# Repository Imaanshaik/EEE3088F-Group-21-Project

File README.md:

# EEE3088F-Group-21-Project

Micro-mouse Sensing and Power Modules
Welcome to the GitHub repository for the Sensing and Power Modules of the Micro-mouse project. This repository contains the design files, documentation, and code related to the development of the sensor and power subsystems for the Micro-mouse robot.

Repository Contents:
Sensing Module:

Schematics
PCB design files
Bill of Materials (BOM)
Code for sensor data processing
Power Module:

Power circuit schematics
PCB layout files
Power management code
Documentation:

Interim Design Report
Final Report
README file
Getting Started:
To get started with the project, follow these steps:

Clone the repository to your local machine:

git clone (https://github.com/Imaanshaik/EEE3088F-Group-21-Project)
Navigate to the respective folders for the Sensing and Power Modules to access the design files and documentation.

Review the README files within each module for specific instructions on setup and usage.

Contributing:
If you would like to contribute to the development of the Sensing and Power Modules, please follow these guidelines:

Fork the repository to your GitHub account.
Create a new branch for your feature or bug fix:
git checkout -b feature/new-feature
Make your changes and commit them with descriptive messages:
git commit -m "Add new sensor calibration code"
Push your changes to your fork:
git push origin feature/new-feature
Open a pull request to merge your changes into the main repository.
Contact:
For any questions or feedback regarding the Sensing and Power Modules, please contact us at [mxxsaf002@myuct.ac.za (sensing module) and shkima005@myuct.ac.za (power module)].

We look forward to collaborating with you on this exciting project!

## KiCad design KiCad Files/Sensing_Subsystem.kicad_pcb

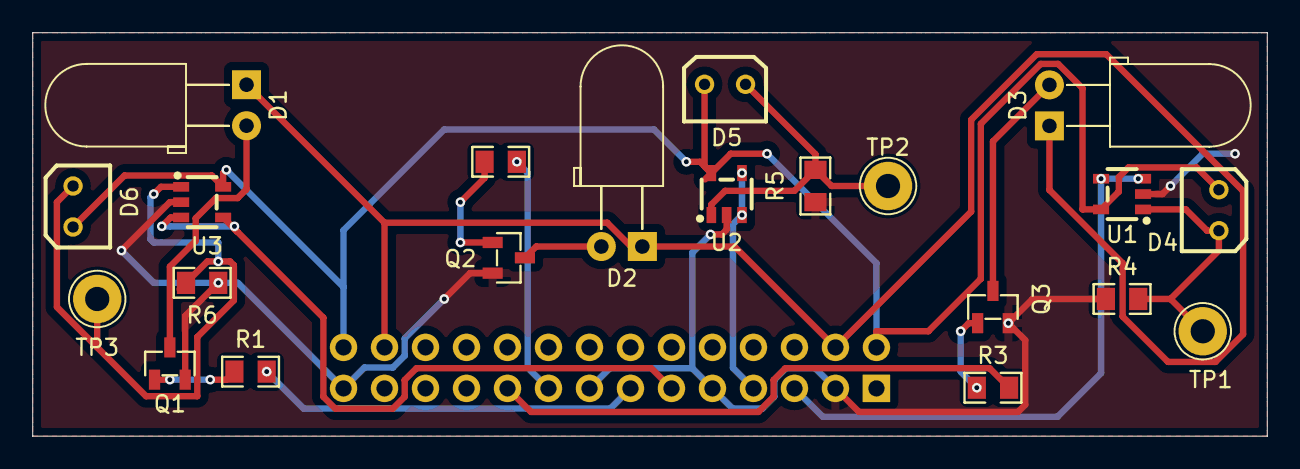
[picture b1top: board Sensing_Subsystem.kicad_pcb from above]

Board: 2 copper layers, 76.5 x 25.0 mm, 22 parts (1 on the bottom side), 18 nets.

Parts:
D1, D2, D3: SFH 4544; LED_D5.0mm_Horizontal_O3.81mm_Z15.0mm
D4, D5, D6: BPW41N; SENSOR-TH_BPW41N
J1: Conn_02x14_Odd_Even; PinHeader_2x14_P2.54mm_Vertical
Q1, Q2, Q3: MMBT2222A_C8512; babytransistor
R1, R2, R3: 6.8k; 6.8kresistor
R4, R5, R6: 1M; 6.8kresistor
TP1, TP2, TP3: TestPoint; TestPoint_THTPad_D3.0mm_Drill1.5mm
U1, U2, U3: LMV321IDBVR; opamp

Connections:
+3.3V: D4.2 (C), D5.2 (C), D6.2 (C), J1.2, J1.28, U1.5 (V+), U2.5 (V+), U3.5 (V+)
BATT: D1.1 (A), D2.1 (A), D3.1 (A), J1.4, J1.26
GND: J1.3, J1.9, J1.15, J1.27, Q1.2 (E), Q2.2 (E), Q3.2 (E), R4.1, R5.1, R6.1, U1.2 (GND), U2.2 (GND), U3.2 (GND)
unnamed: D1.2 (C), Q1.3 (C)
unnamed: D2.2 (C), Q2.3 (C)
unnamed: D3.2 (C), Q3.3 (C)
unnamed: D4.1 (A), R4.2, TP1.1, U1.1 (+)
unnamed: D5.1 (A), R5.2, TP2.1, U2.1 (+)
unnamed: D6.1 (A), R6.2, TP3.1, U3.1 (+)
unnamed: Q1.1 (B), R1.2
unnamed: Q2.1 (B), R2.2
unnamed: Q3.1 (B), R3.2
PA3: J1.5, U1.3 (-), U1.4 (OUT)
PA4: J1.7, U2.3 (-), U2.4 (OUT)
PA5: J1.11, U3.3 (-), U3.4 (OUT)
PA6: J1.13, R1.1
PA7: J1.17, R2.1
PC4: J1.19, R3.1

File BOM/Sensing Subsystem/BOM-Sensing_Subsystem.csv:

Comment,Designator,Footprint,LCSC
BPW41N,"D4,D5,D6",SENSOR-TH_BPW41N,C142586
1M,"R4,R5,R6",6.8kresistor,C17514
6.8k,"R1,R2,R3",6.8kresistor,C17772
SFH 4544,"D1,D2,D3",LED_D5.0mm_Horizontal_O3.81mm_Z15.0mm,C2900370
LMV321IDBVR,"U1,U2,U3",opamp,C7972
MMBT2222A_C8512,"Q1,Q2,Q3",babytransistor,C8512
TestPoint,TP2,TestPoint_THTPad_D3.0mm_Drill1.5mm,
TestPoint,TP3,TestPoint_THTPad_D3.0mm_Drill1.5mm,
TestPoint,TP1,TestPoint_THTPad_D3.0mm_Drill1.5mm,
Conn_02x14_Odd_Even,J1,PinHeader_2x14_P2.54mm_Vertical,

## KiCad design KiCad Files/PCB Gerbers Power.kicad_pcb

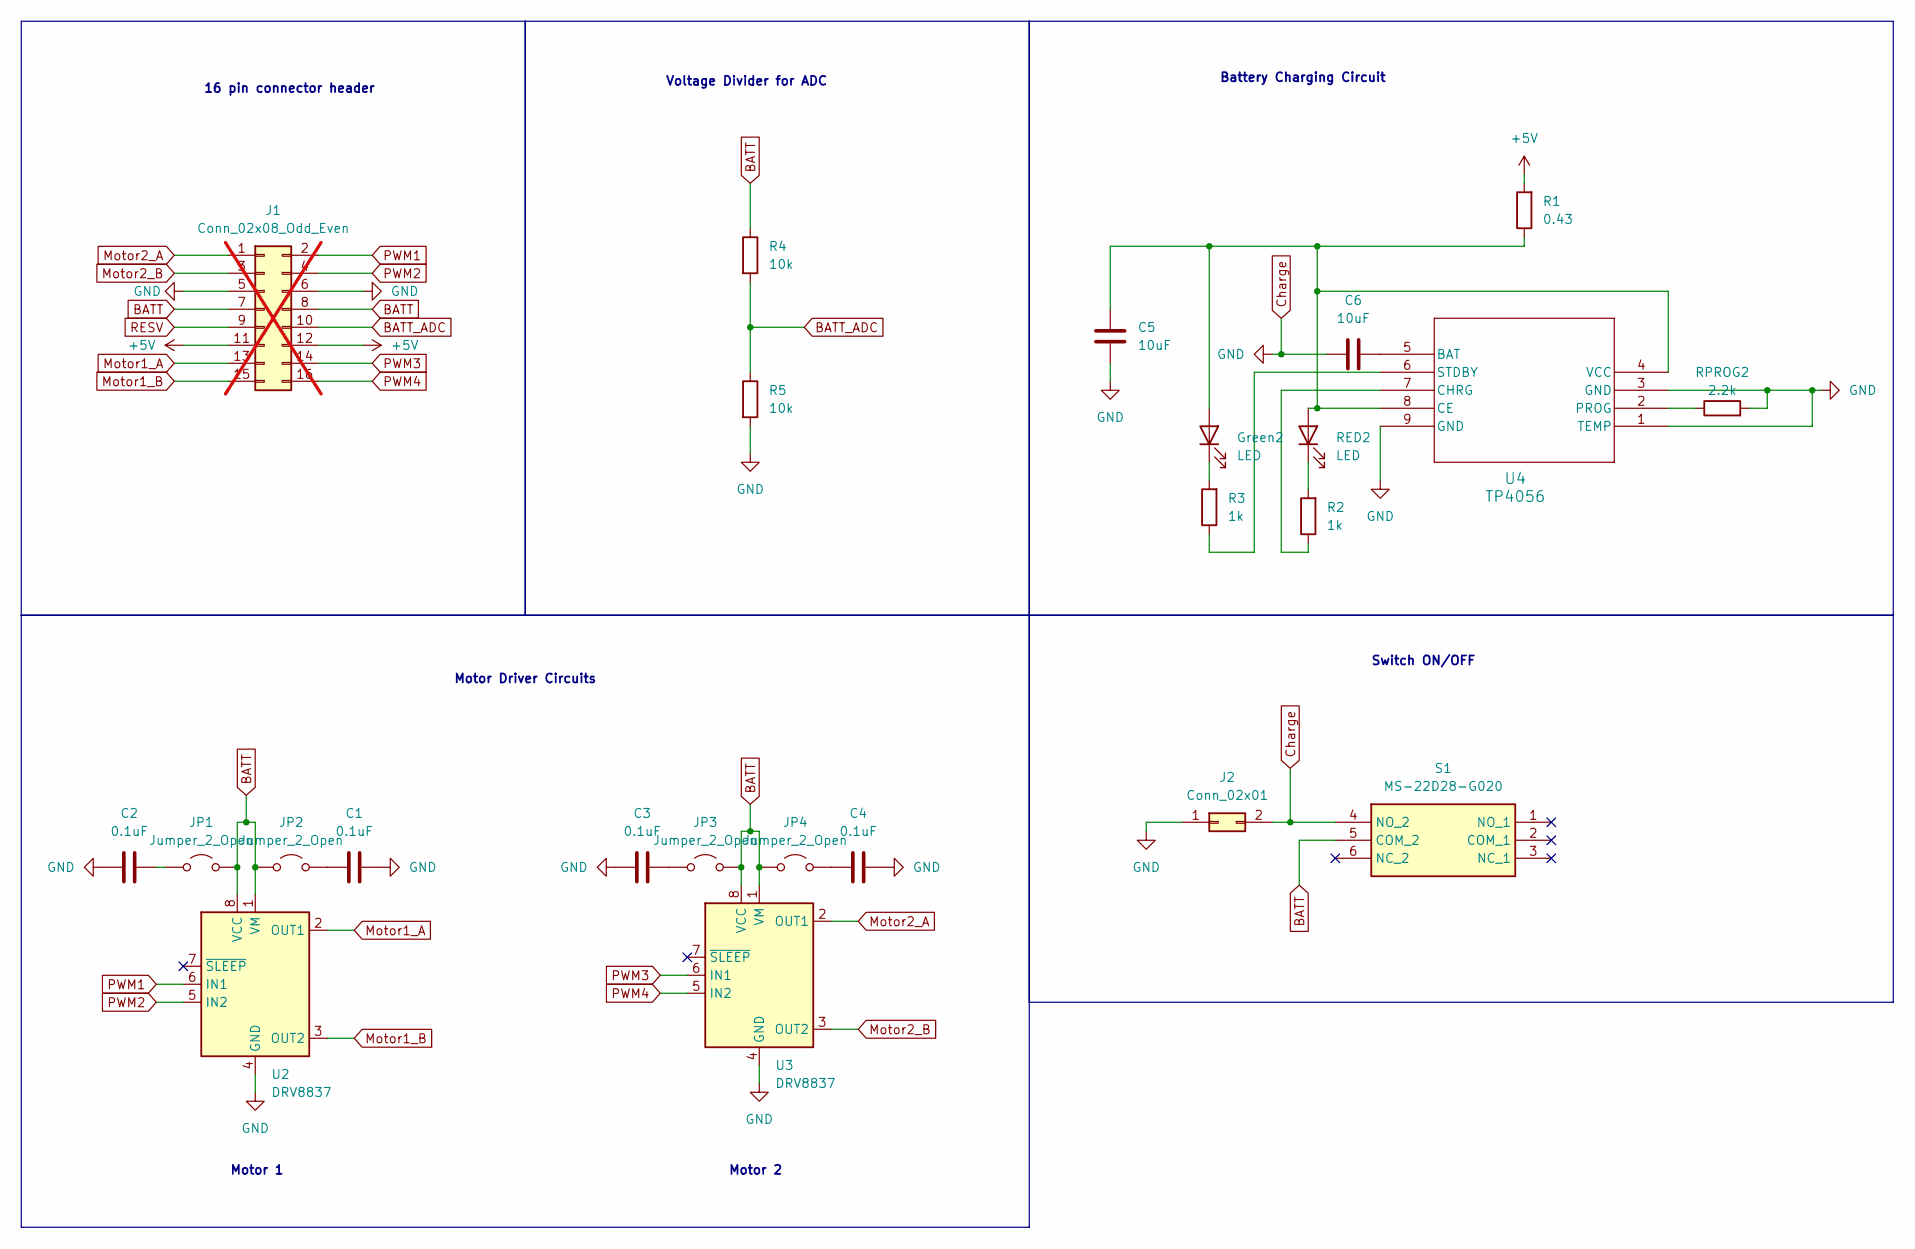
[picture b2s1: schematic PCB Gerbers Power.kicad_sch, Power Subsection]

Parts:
C1, C2, C3, C4: 0.1uF; C_0805_2012Metric
C5, C6: 10uF; C_0805_2012Metric
Green2: LED; D_0805_2012Metric
J1: Conn_02x08_Odd_Even; PinHeader_2x08_P2.54mm_Vertical; not fitted
J2: Conn_02x01; PinHeader_2x01_P2.00mm_Vertical
JP1, JP2, JP3, JP4: Jumper_2_Open; SolderJumper-2_P1.3mm_Open_Pad1.0x1.5mm
R1: 0.43; R_0805_2012Metric
R2, R3: 1k; R_0805_2012Metric
R4, R5: 10k; R_0805_2012Metric
RED2: LED; D_0805_2012Metric
RPROG2: 2.2k; R_0805_2012Metric
S1: MS-22D28-G020; MS22D28G020 switch; Manufacturer_Part_Number MS-22D28-G020
U2, U3: DRV8837; WSON-8-1EP_2x2mm_P0.5mm_EP0.9x1.6mm
U4: TP4056

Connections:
+5V: J1.11, J1.12, R1.2
BATT: J1.7, J1.8, JP1.2 (B), JP2.1 (A), JP3.2 (B), JP4.1 (A), R4.1, S1.5 (COM_2), U2.1 (VM), U2.8 (VCC), U3.1 (VM), U3.8 (VCC)
BATT_ADC: J1.10, R4.2, R5.1
Charge: C1.2, C2.1, C3.1, C4.2, C5.2, C6.1, J1.5, J1.6, J2.1, J2.2, R5.2, RPROG2.2, S1.4 (NO_2), U2.4 (GND), U2.9 (GND), U3.4 (GND), U3.9 (GND), U4.1 (TEMP), U4.3 (GND), U4.9 (GND)
Motor1_A: J1.13, U2.2 (OUT1)
Motor1_B: J1.15, U2.3 (OUT2)
Motor2_A: J1.1, U3.2 (OUT1)
Motor2_B: J1.3, U3.3 (OUT2)
unnamed: C5.1, Green2.2 (A), R1.1, RED2.2 (A), U4.4 (VCC), U4.8 (CE)
unnamed: Green2.1 (K), R3.2
unnamed: C2.2, JP1.1 (A)
unnamed: C1.1, JP2.2 (B)
unnamed: C3.2, JP3.1 (A)
unnamed: C4.1, JP4.2 (B)
unnamed: R2.2, RED2.1 (K)
unnamed: C6.2, U4.5 (BAT)
unnamed: R2.1, U4.7 (CHRG)
unnamed: RPROG2.1, U4.2 (PROG)
unnamed: R3.1, U4.6 (STDBY)
PWM1: J1.2, U2.6 (IN1)
PWM2: J1.4, U2.5 (IN2)
PWM3: J1.14, U3.6 (IN1)
PWM4: J1.16, U3.5 (IN2)
RESV: J1.9

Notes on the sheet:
Motor Driver Circuits
Voltage Divider for ADC
Battery Charging Circuit
16 pin connector header
Switch ON/OFF
Motor 1
Motor 2

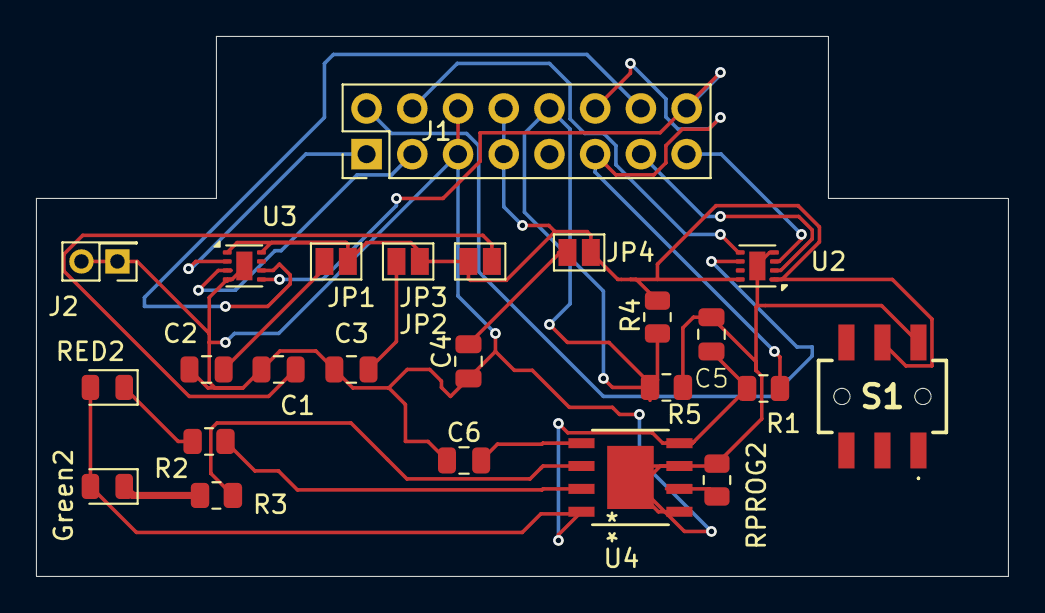
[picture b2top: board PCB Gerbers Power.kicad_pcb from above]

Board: 2 copper layers, 54.0 x 30.0 mm, 24 parts (0 on the bottom side), 23 nets.

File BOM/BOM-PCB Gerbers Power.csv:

Comment,Designator,Footprint,LCSC
MS-22D28-G020,S1,MS22D28G020 switch,
DRV8837,U3,WSON-8-1EP_2x2mm_P0.5mm_EP0.9x1.6mm,
Conn_02x08_Odd_Even,J1,PinHeader_2x08_P2.54mm_Vertical,
1k,R3,R_0805_2012Metric,
Jumper_2_Open,JP4,SolderJumper-2_P1.3mm_Open_Pad1.0x1.5mm,
1k,R2,R_0805_2012Metric,
TP4056,U4,TP4056,
2.2k,RPROG2,R_0805_2012Metric,
DRV8837,U2,WSON-8-1EP_2x2mm_P0.5mm_EP0.9x1.6mm,
LED,RED2,D_0805_2012Metric,
10k,R5,R_0805_2012Metric,
Jumper_2_Open,JP1,SolderJumper-2_P1.3mm_Open_Pad1.0x1.5mm,
0.1uF,C2,C_0805_2012Metric,
10uF,C5,C_0805_2012Metric,
10k,R4,R_0805_2012Metric,
10uF,C6,C_0805_2012Metric,
Jumper_2_Open,JP3,SolderJumper-2_P1.3mm_Open_Pad1.0x1.5mm,
0.1uF,C1,C_0805_2012Metric,
0.1uF,C4,C_0805_2012Metric,
0.1uF,C3,C_0805_2012Metric,
Conn_02x01,J2,PinHeader_2x01_P2.00mm_Vertical,
LED,Green2,D_0805_2012Metric,
Jumper_2_Open,JP2,SolderJumper-2_P1.3mm_Open_Pad1.0x1.5mm,
2.2k,R1,R_0805_2012Metric,

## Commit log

2024-04-21 Create Power schematic
2024-04-21 Create files
2024-04-21 gerbers
2024-04-21 power subsystem
2024-04-21 bill of materials
2024-04-21 Create Sensing Module Gerbers
2024-04-21 Create Sensor Module Gerbers
2024-04-21 Create Sensing Subsystem BOM
